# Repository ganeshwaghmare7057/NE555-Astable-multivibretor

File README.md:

# NE555-Astable-multivibretor
  Description: The aim of an astable multivibrator using a 555 timer is to create a continuous square wave output. The 555 timer is an integrated circuit.that's used in oscillator circuits to provide timing delays. The 555 timer works by charging and discharging a capacitor through two resistors, and then triggering an internal flip-flop when the capacitor voltage reaches a certain level. The frequency of the square wave is determined by the values of the resistor and capacitor.

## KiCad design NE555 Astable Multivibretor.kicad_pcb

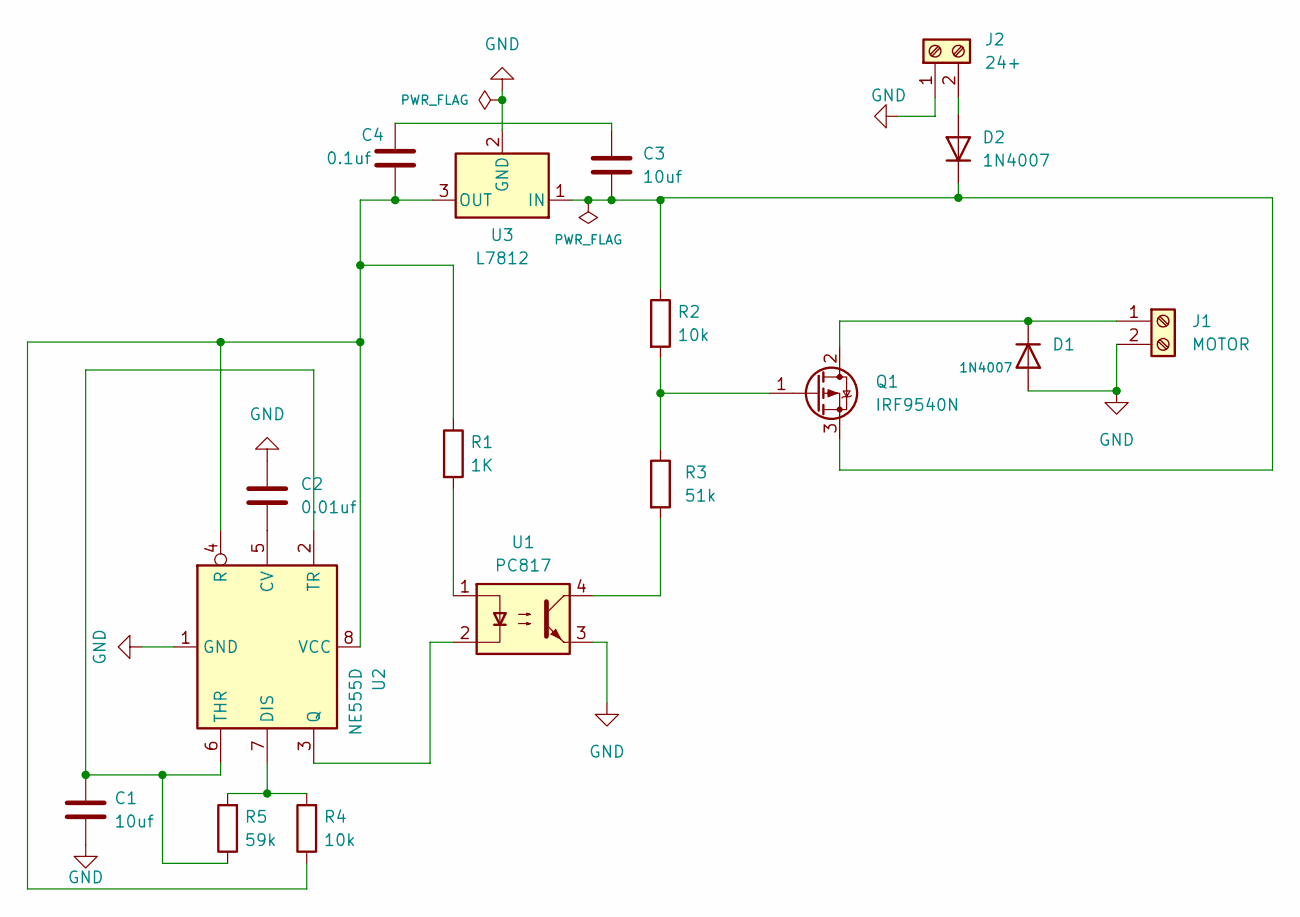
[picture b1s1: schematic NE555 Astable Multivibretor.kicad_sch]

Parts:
C1, C3: 10uf; CP_Radial_D6.3mm_P2.50mm
C2: 0.01uf; CP_Radial_D6.3mm_P2.50mm
C4: 0.1uf; CP_Radial_D6.3mm_P2.50mm
D1, D2: 1N4007; D_DO-41_SOD81_P10.16mm_Horizontal
J1: MOTOR; TerminalBlock_4Ucon_1x02_P3.50mm_Horizontal
J2: 24+; TerminalBlock_4Ucon_1x02_P3.50mm_Horizontal
Q1: IRF9540N; TO-220-3_Vertical
R1: 1K; R_Axial_DIN0204_L3.6mm_D1.6mm_P5.08mm_Horizontal
R2, R4: 10k; R_Axial_DIN0204_L3.6mm_D1.6mm_P5.08mm_Horizontal
R3: 51k; R_Axial_DIN0204_L3.6mm_D1.6mm_P5.08mm_Horizontal
R5: 59k; R_Axial_DIN0204_L3.6mm_D1.6mm_P5.08mm_Horizontal
U1: PC817; DIP-4_W7.62mm
U2: NE555D; DIP254P762X533-8
U3: L7812; TO-220-3

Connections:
GND: C1.1, C2.1, D1.2 (A), J1.2, J2.1, U1.3, U2.1 (GND), U3.2 (GND)
unnamed: C3.1, C4.1
unnamed: D1.1 (K), J1.1, Q1.2 (D)
unnamed: D2.2 (A), J2.2
unnamed: C3.2, D2.1 (K), Q1.3 (S), R2.1, U3.1 (IN)
unnamed: Q1.1 (G), R2.2, R3.1
unnamed: R1.2, U1.1
unnamed: R3.2, U1.4
unnamed: C2.2, U2.5 (CV)
unnamed: R4.2, R5.2, U2.7 (DIS)
unnamed: U1.2, U2.3 (Q)
unnamed: C4.2, R1.1, R4.1, U2.4 (R), U2.8 (VCC), U3.3 (OUT)
unnamed: C1.2, R5.1, U2.2 (TR), U2.6 (THR)

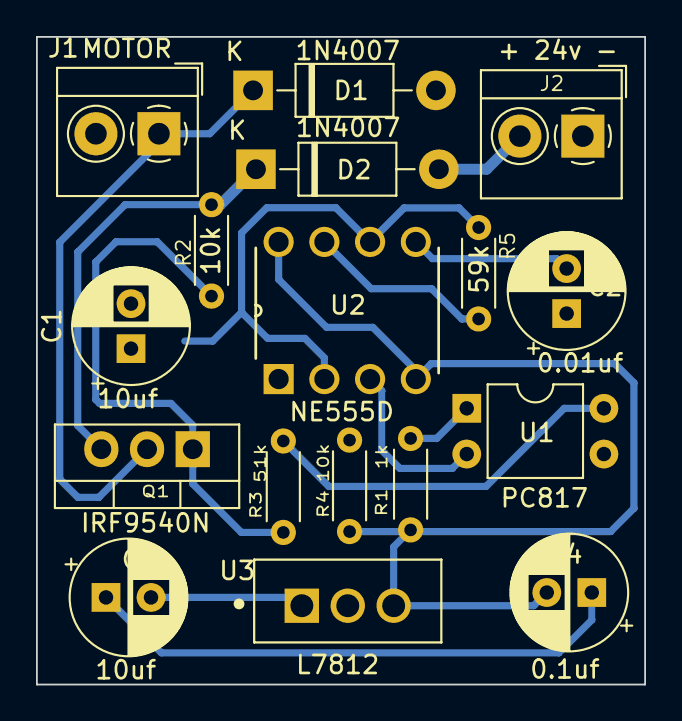
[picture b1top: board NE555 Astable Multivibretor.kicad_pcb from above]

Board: 2 copper layers, 33.8 x 36.0 mm, 17 parts (0 on the bottom side), 13 nets.
